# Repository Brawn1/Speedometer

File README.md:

# Hot Wheels Speedometer

Arduino Nano basierter Geschwindigkeitsmesser fuer Hot Wheels Strecken. Zwei IR-Sensoren im Abstand von 10 cm messen die Durchfahrtszeit und ein Servomotor zeigt die Geschwindigkeit auf einer analogen Skala an.

## Features

- Geschwindigkeitsmessung ueber zwei IR-Sensoren (10 cm Abstand)
- Analoge Tacho-Anzeige mit Servomotor
- Einstellbarer Servo-Ausschlag ueber 4 DIP-Switches (Multiplikator 1.0x - 5.0x)
- Batterieueberwachung mit Rot/Gruen LED (3.7V Li-Ion Akku)
- Sensor-Status LEDs (zeigen Sensor 1/2 Ausloesung an)
- Startup-Melodie ueber Piezo-Lautsprecher
- Serial Monitor Ausgabe fuer Debugging (9600 Baud)

## Hardware

### Komponenten

| Komponente | Anzahl |
|---|---|
| Arduino Nano | 1 |
| IR-Sensor (digital) | 2 |
| Servomotor | 1 |
| Piezo-Lautsprecher | 1 |
| 4-fach DIP-Switch | 1 |
| LED gruen (Batterie OK) | 1 |
| LED rot (Batterie niedrig) | 1 |
| LED (Sensor 1 Status) | 1 |
| LED (Sensor 2 Status) | 1 |
| Widerstand 10k Ohm | 2 |
| 3.7V Li-Ion Akku | 1 |

### Pin-Belegung

| Pin | Funktion |
|---|---|
| D2 | IR-Sensor 1 (Start) |
| D3 | IR-Sensor 2 (Ziel) |
| D4 | LED gruen (Batterie OK) |
| D5 | LED rot (Batterie niedrig) |
| D6 | LED Sensor 1 |
| D7 | LED Sensor 2 |
| D8 | Piezo-Lautsprecher |
| D9 | Servomotor |
| D10 | DIP-Switch 1 (Wert 1) |
| D11 | DIP-Switch 2 (Wert 2) |
| D12 | DIP-Switch 3 (Wert 4) |
| D13 | DIP-Switch 4 (Wert 8) |
| A0 | Batteriespannung (Spannungsteiler) |

### Spannungsteiler (Batteriemessung)

Die Batteriespannung wird ueber einen Spannungsteiler mit 2x 10k Ohm Widerstaenden gemessen. Der Spannungsteiler halbiert die Batteriespannung, damit sie im ADC-Messbereich des Arduino liegt.

```
Batterie+ ---[R1 10k]---+---[R2 10k]--- GND
                         |
                         A0
```

### DIP-Switch Anschluss

Die DIP-Switches nutzen die internen Pull-Up Widerstaende des Arduino. Jeder Schalter verbindet den Pin mit GND wenn aktiv.

```
Pin D10-D13 ---[DIP-Switch]--- GND
```

## DIP-Switch Multiplikator-Tabelle

Die 4 DIP-Switches steuern den Servo-Ausschlag mit 16 Stufen:

| DIP 4-3-2-1 | Wert | Multiplikator |
|---|---|---|
| 0000 | 0 | 1.0x |
| 0001 | 1 | 1.27x |
| 0010 | 2 | 1.53x |
| 0011 | 3 | 1.8x |
| 0100 | 4 | 2.07x |
| 0101 | 5 | 2.33x |
| 0110 | 6 | 2.6x |
| 0111 | 7 | 2.87x |
| 1000 | 8 | 3.13x |
| 1001 | 9 | 3.4x |
| 1010 | 10 | 3.67x |
| 1011 | 11 | 3.93x |
| 1100 | 12 | 4.2x |
| 1101 | 13 | 4.47x |
| 1110 | 14 | 4.73x |
| 1111 | 15 | 5.0x |

## Batterieueberwachung

| Spannung | Status | LED |
|---|---|---|
| > 3.6V | OK | Gruen |
| 3.4V - 3.6V | Niedrig | Rot |
| < 3.4V | Schwach | Rot |

Die Batterie wird alle 30 Sekunden geprueft. Die Messung erfolgt mit 16-fachem Oversampling fuer stabile Werte und wird nur durchgefuehrt wenn der Servo nicht aktiv ist.

## Messablauf

1. Einschalten: Startup-Melodie, Servo faehrt auf Startposition, Batterie wird geprueft
2. Auto faehrt durch Sensor 1: LED Sensor 1 leuchtet, Messung startet
3. Auto faehrt durch Sensor 2: LED Sensor 2 leuchtet, Geschwindigkeit wird berechnet
4. Servo zeigt Geschwindigkeit an (2 Sekunden)
5. Servo faehrt zurueck, beide Sensor-LEDs erlischen
6. Bereit fuer naechste Messung

Bei Timeout (Sensor 2 nicht innerhalb von 4 Sekunden ausgeloest) wird die Messung abgebrochen.

## Projektstruktur

```
Speedometer/
├── Code/speedometer/speedometer.ino   # Arduino Sketch
├── Kicad/                             # KiCad Schaltplan
├── Case/                              # Gehaeuse (FreeCAD)
├── LICENSE
└── README.md
```

## Lizenz

Siehe [LICENSE](LICENSE).

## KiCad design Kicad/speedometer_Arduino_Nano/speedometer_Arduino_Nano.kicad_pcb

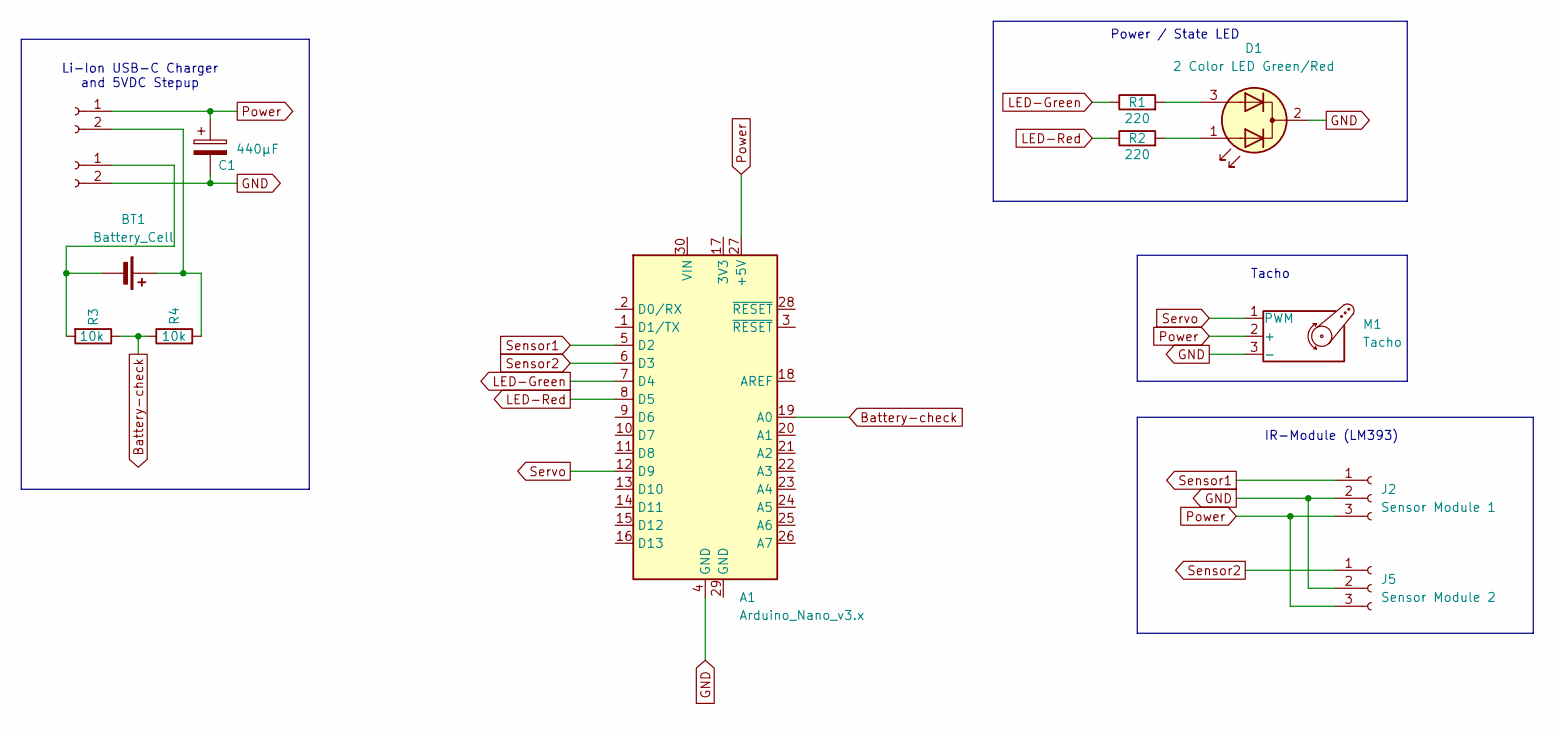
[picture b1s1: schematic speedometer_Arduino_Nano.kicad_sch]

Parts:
A1: Arduino_Nano_v3.x; Arduino_Nano
BT1: Battery_Cell; BatteryHolder_Keystone_1042_1x18650
C1: 440µF; CP_Radial_D10.0mm_P5.00mm
D1: 2 Color LED Green/Red; LED_D5.0mm-3
J1, J3: Conn_01x02_Socket; PinSocket_1x02_P2.54mm_Vertical
J2: Sensor Module 1; PinHeader_1x03_P2.54mm_Vertical
J5: Sensor Module 2; PinHeader_1x03_P2.54mm_Vertical
M1: Tacho; PinHeader_1x03_P2.54mm_Vertical
R1, R2: 220; R_Axial_DIN0207_L6.3mm_D2.5mm_P10.16mm_Horizontal
R3, R4: 10k; R_Axial_DIN0207_L6.3mm_D2.5mm_P10.16mm_Horizontal

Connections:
Battery-check: A1.19 (A0), R3.1, R4.1
GND: A1.4 (GND), C1.2, D1.2 (K), J2.2, J3.2, J5.2, M1.3 (-)
LED-Green: A1.7 (D4), R1.1
LED-Red: A1.8 (D5), R2.1
unnamed: BT1.1 (+), J1.2, R4.2
unnamed: BT1.2 (-), J3.1, R3.2
unnamed: D1.1 (A1), R2.2
unnamed: D1.3 (A2), R1.2
Power: A1.27 (+5V), C1.1, J1.1, J2.3, J5.3, M1.2 (+)
Sensor1: A1.5 (D2), J2.1
Sensor2: A1.6 (D3), J5.1
Servo: A1.12 (D9), M1.1 (PWM)

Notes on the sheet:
IR-Module (LM393)
Power / State LED
Tacho
Li-Ion USB-C Charger and 5VDC Stepup

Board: 2 copper layers, 13 parts (0 on the bottom side), 12 nets, no tracks yet.

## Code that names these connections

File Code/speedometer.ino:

#include <Servo.h>

// Pin-Definitionen
const int SENSOR1_PIN = 2;  // Erster IR-Sensor (Digital Pin)
const int SENSOR2_PIN = 3;  // Zweiter IR-Sensor (Digital Pin)
const int SERVO_PIN = 9;    // Servo Motor Pin

// Konstanten
const float DISTANCE_CM = 10.0;  // Abstand zwischen Sensoren in cm
const int SERVO_MIN_ANGLE = 0;   // Minimaler Servo-Winkel
const int SERVO_MAX_ANGLE = 180; // Maximaler Servo-Winkel
const float MAX_SPEED_KMH = 20.0; // Maximale erwartete Geschwindigkeit in km/h

// Variablen
Servo speedServo;
unsigned long sensor1Time = 0;
unsigned long sensor2Time = 0;
bool sensor1Triggered = false;
bool measurementActive = false;

void setup() {
  // Serial Monitor initialisieren
  Serial.begin(9600);
  Serial.println("Geschwindigkeitsmessung gestartet");
  Serial.println("Sensorabstand: 10cm");
  Serial.println("------------------------");
  
  // Pins konfigurieren
  pinMode(SENSOR1_PIN, INPUT);
  pinMode(SENSOR2_PIN, INPUT);
  
  // Servo initialisieren
  speedServo.attach(SERVO_PIN);
  speedServo.write(0);  // Servo auf 0° setzen
  
  delay(1000);
}

void loop() {
  // Sensor 1 prüfen (Start der Messung)
  if (digitalRead(SENSOR1_PIN) == LOW && !measurementActive) {
    sensor1Time = millis();
    sensor1Triggered = true;
    measurementActive = true;
    Serial.println("Sensor 1 ausgelöst - Messung gestartet");
  }
  
  // Sensor 2 prüfen (Ende der Messung)
  if (digitalRead(SENSOR2_PIN) == LOW && measurementActive && sensor1Triggered) {
    sensor2Time = millis();
    
    // Zeit zwischen Sensoren berechnen
    unsigned long timeDiff = sensor2Time - sensor1Time;
    
    // Geschwindigkeit berechnen
    if (timeDiff > 0) {
      // Geschwindigkeit in cm/ms
      float speedCmPerMs = DISTANCE_CM / (float)timeDiff;
      
      // Umrechnung in km/h
      float speedKmh = speedCmPerMs * 3600.0;
      
      // Umrechnung in m/s
      float speedMs = speedCmPerMs * 10.0;
      
      // Ergebnisse ausgeben
      Serial.println("------------------------");
      Serial.print("Zeit: ");
      Serial.print(timeDiff);
      Serial.println(" ms");
      Serial.print("Geschwindigkeit: ");
      Serial.print(speedKmh, 2);
      Serial.print(" km/h (");
      Serial.print(speedMs, 2);
      Serial.println(" m/s)");
      Serial.println("------------------------");
      
      // Servo-Position berechnen und setzen
      int servoAngle = calculateServoAngle(speedKmh);
      speedServo.write(servoAngle);
      Serial.print("Servo-Position: ");
      Serial.print(servoAngle);
      Serial.println("°");
      Serial.println();
    }
    
    // Reset für nächste Messung
    sensor1Triggered = false;
    measurementActive = false;
    
    // Kurze Verzögerung um Mehrfachauslösungen zu vermeiden
    delay(1000);
    
    // Servo zurücksetzen
    speedServo.write(0);
  }
  
  // Timeout: Wenn Sensor 2 nicht innerhalb von 5 Sekunden ausgelöst wird
  if (measurementActive && (millis() - sensor1Time > 5000)) {
    Serial.println("Timeout - Messung abgebrochen");
    measurementActive = false;
    sensor1Triggered = false;
    speedServo.write(0);
  }
  
  delay(10);  // Kleine Verzögerung für Stabilität
}

// Funktion zur Berechnung des Servo-Winkels basierend auf Geschwindigkeit
int calculateServoAngle(float speedKmh) {
  // Begrenze Geschwindigkeit auf Maximum
  if (speedKmh > MAX_SPEED_KMH) {
    speedKmh = MAX_SPEED_KMH;
  }
  
  // Lineare Abbildung von 0-MAX_SPEED_KMH auf 0-180°
  int angle = (int)((speedKmh / MAX_SPEED_KMH) * SERVO_MAX_ANGLE);
  
  // Begrenze Winkel auf gültigen Bereich
  if (angle < SERVO_MIN_ANGLE) angle = SERVO_MIN_ANGLE;
  if (angle > SERVO_MAX_ANGLE) angle = SERVO_MAX_ANGLE;
  
  return angle;
}

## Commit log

2026-01-09 Add Arduino speed measurement code with IR sensors and servo display
2026-01-09 patched on arduino uno
2026-01-09 update servo
2026-01-09 Add debouncing to prevent false sensor triggers from servo noise
2026-01-09 update speedkmh and set maxspeed to 100km/h
2026-01-09 Add battery monitoring with 2-color LED indicator (Green/Red)
2026-01-09 move print string from RAM to Flash
2026-01-10 removed cache and backups
2026-01-10 update gitignore for freeCAD
2026-01-10 added Case Version 0.1
2026-01-11 Removed Rounding on bottom
2026-01-12 update code
2026-01-12 Initial plan
2026-01-12 Optimize servo power management to reduce current consumption
2026-01-12 Refactor: Extract servo reset logic into helper function
2026-01-12 Use constants for servo angles and delays for better maintainability
2026-01-12 Fix incorrect speed conversion formulas from cm/ms to km/h and m/s
2026-01-12 Improve conversion formula comments for clarity
2026-01-12 added multiplier to use as Toy
2026-01-13 changed multiplier to 3
2026-01-13 added Tacho Image
2026-01-13 Fix typo in project description
2026-01-13 Add documentation and constants for battery voltage calculation
    - Added ADC_REFERENCE_VOLTAGE constant (5.0V) to clarify Arduino reference voltage
    - Added VOLTAGE_DIVIDER_RATIO constant (2.0) to document voltage divider configuration
    - Added ADC_MAX_VALUE constant (1023.0) for 10-bit ADC
    - Enhanced comments in checkBattery() to explain each step of the voltage calculation
    - Replaced magic numbers with named constants for better code maintainability
    The calculation (sensorValue / 1023.0) * 5.0 * 2.0 is correct:
2026-01-13 Update ADC reference voltage to measured value of 4.457V
    The Arduino Nano is running at 4.457V DC (not 5V), which affects the ADC reference voltage. Updated the ADC_REFERENCE_VOLTAGE constant from 5.0 to 4.457 to match the actual measured voltage for accur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
2026-01-13 convert multiplier to float
2026-03-01 erweiterung Readme.md code
2026-04-05 case v2
